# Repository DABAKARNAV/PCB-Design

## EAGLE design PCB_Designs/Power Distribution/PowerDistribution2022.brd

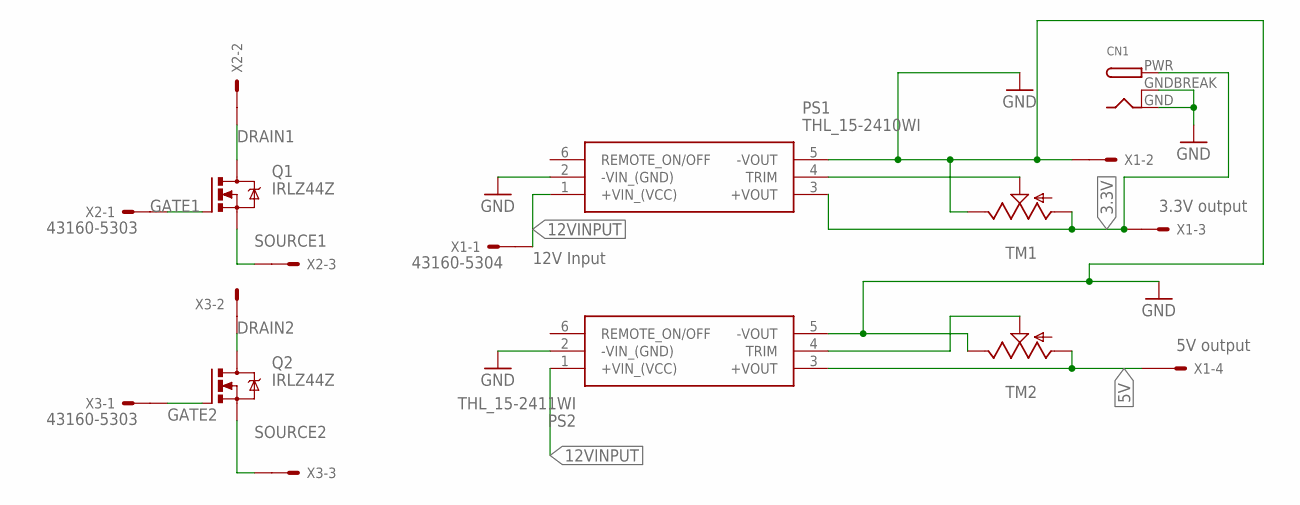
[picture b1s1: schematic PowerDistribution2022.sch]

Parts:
CN1: DCBARRELPTH; DCJACK_2MM_PTH
PS1: THL_15-2410WI; THL152410WI
PS2: THL_15-2411WI; THL152411WI
Q1, Q2: IRLZ44Z; TO220BH
TM1, TM2: TRIM; 6MM
X1: 43160-5304; 43160-XX04
X2, X3: 43160-5303; 43160-XX03

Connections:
3.3V: CN1.PWR, PS1.3 (+VOUT), TM1.A, X1.3@1
5V: PS2.3 (+VOUT), TM2.A, X1.4@1
12VINPUT: PS1.1 (+VIN_(VCC)), PS2.1 (+VIN_(VCC)), X1.1@1
DRAIN1: Q1.D, X2.2@1
DRAIN2: Q2.D, X3.2@1
GATE1: Q1.G, X2.1@1
GATE2: Q2.G, X3.1@1
GND: CN1.GND, CN1.GNDBREAK, PS1.2 (-VIN_(GND)), PS1.5 (-VOUT), PS2.2 (-VIN_(GND)), PS2.5 (-VOUT), TM1.E, TM2.E, X1.2@1
unnamed: PS1.4 (TRIM), TM1.S
unnamed: PS2.4 (TRIM), TM2.S
SOURCE1: Q1.S, X2.3@1
SOURCE2: Q2.S, X3.3@1

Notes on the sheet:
12V Input
5V output
3.3V output

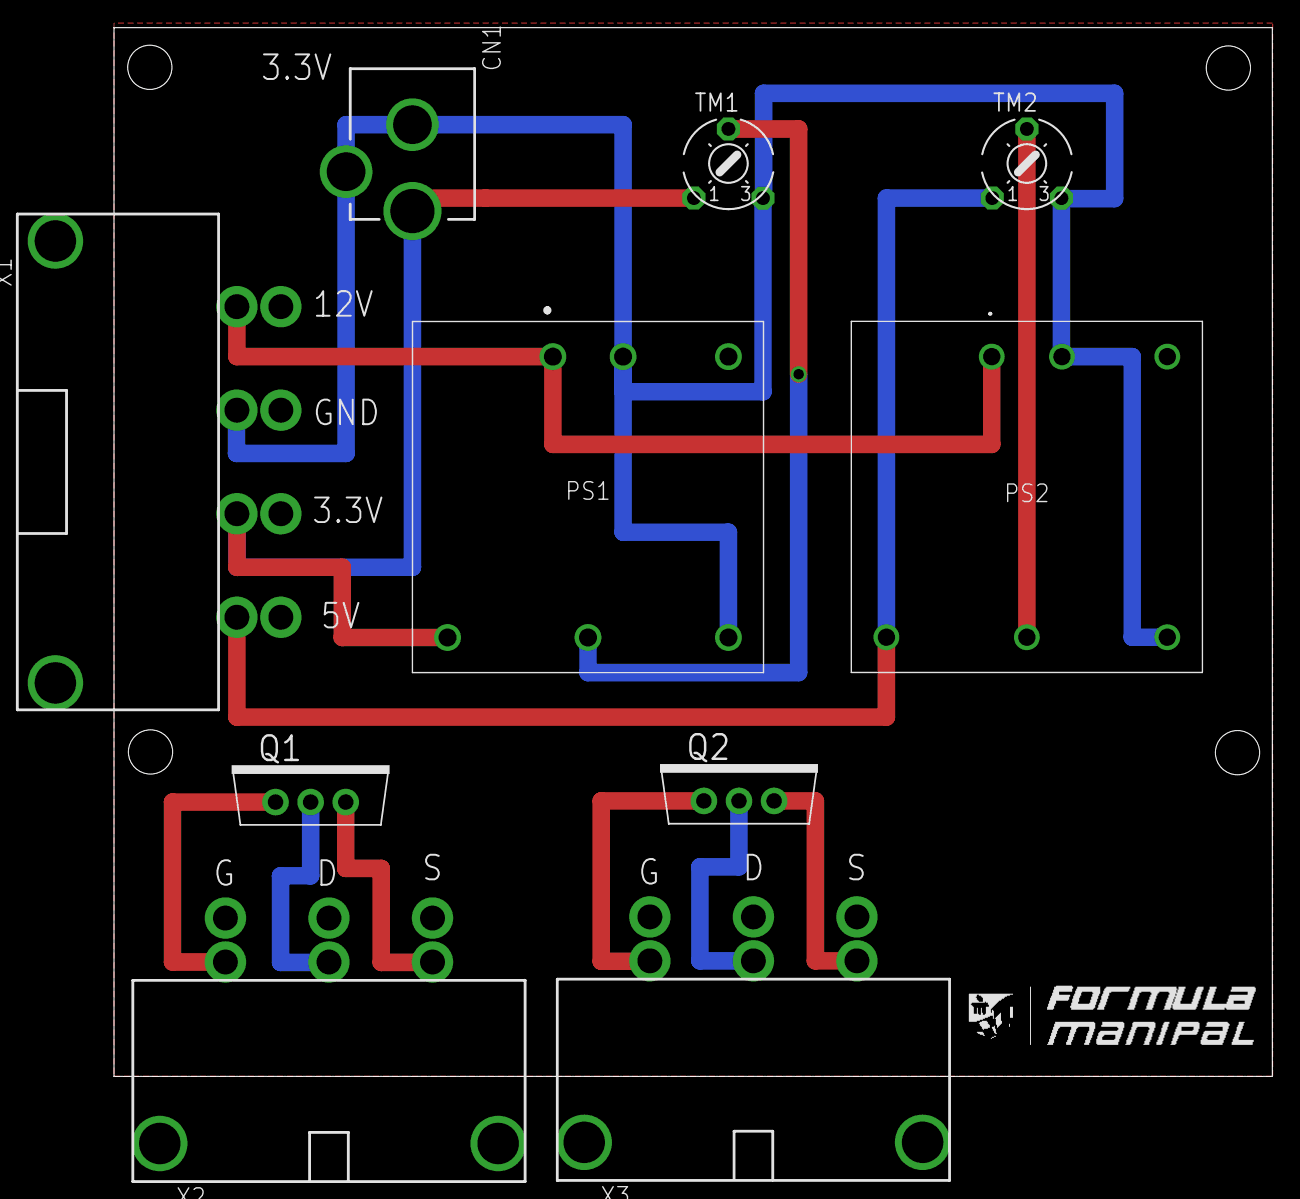
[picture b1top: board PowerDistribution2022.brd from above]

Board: 2 copper layers, 83.8 x 75.9 mm, 10 parts (0 on the bottom side), 12 nets.

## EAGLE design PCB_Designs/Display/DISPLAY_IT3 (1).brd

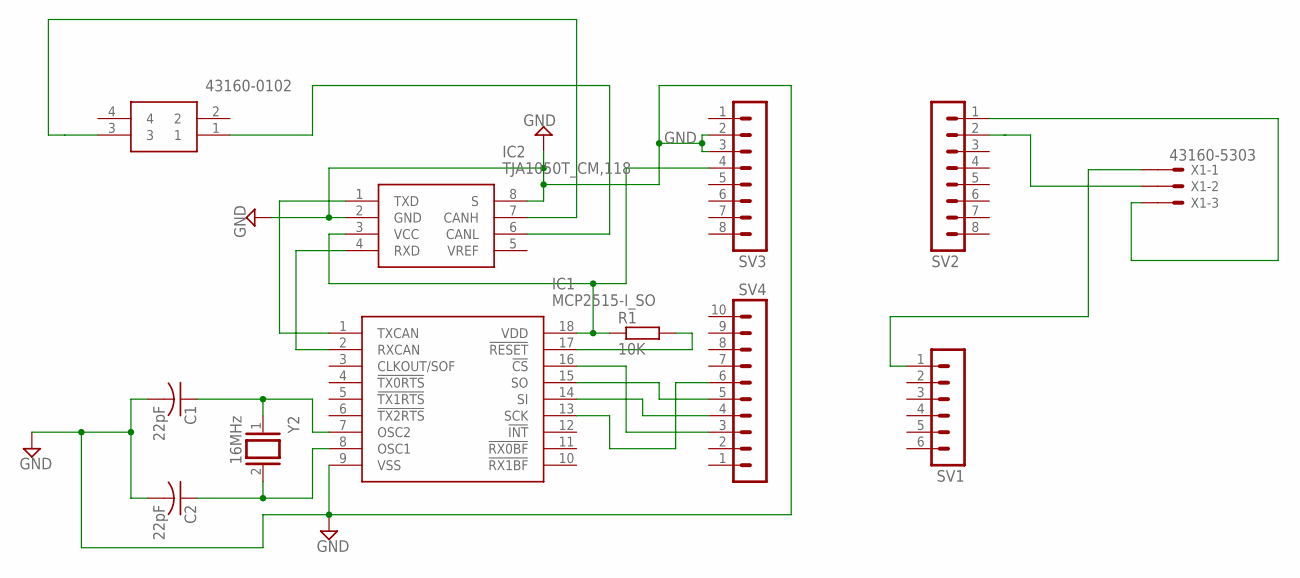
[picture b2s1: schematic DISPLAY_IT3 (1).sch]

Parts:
C1, C2: 22pF; C025-024X044
DIFF_N: 43160-0102; 431600102
IC1: MCP2515-I_SO; SOIC127P1030X265-18N
IC2: TJA1050T_CM,118; SOIC127P600X175-8N
R1: 10K; 0204/7
SV1: MA06-1
SV2, SV3: MA08-1
SV4: MA10-1
X1: 43160-5303; 43160-XX03
Y2: 16MHz; QS

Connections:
DIFF1_N: C2.1, IC1.8 (OSC1), Y2.2
DIFF1_P: C1.1, IC1.7 (OSC2), Y2.1
DIFF_N: DIFF_N.1, IC2.6 (CANL)
DIFF_P: DIFF_N.3, IC2.7 (CANH)
GND: C1.2, C2.2, IC1.9 (VSS), IC2.2 (GND), IC2.8 (S), SV3.2, SV3.3
unnamed: IC1.15 (SO), SV4.5
unnamed: SV2.1, X1.3@1
unnamed: IC1.1 (TXCAN), IC2.1 (TXD)
unnamed: IC1.2 (RXCAN), IC2.4 (RXD)
unnamed: IC1.16 (!CS), SV4.3
unnamed: IC1.14 (SI), SV4.4
unnamed: SV1.1, X1.1@1
unnamed: IC1.13 (SCK), SV4.6
unnamed: IC1.17 (!RESET), R1.2
unnamed: SV2.2, X1.2@1
unnamed: IC1.18 (VDD), IC2.3 (VCC), R1.1, SV3.4

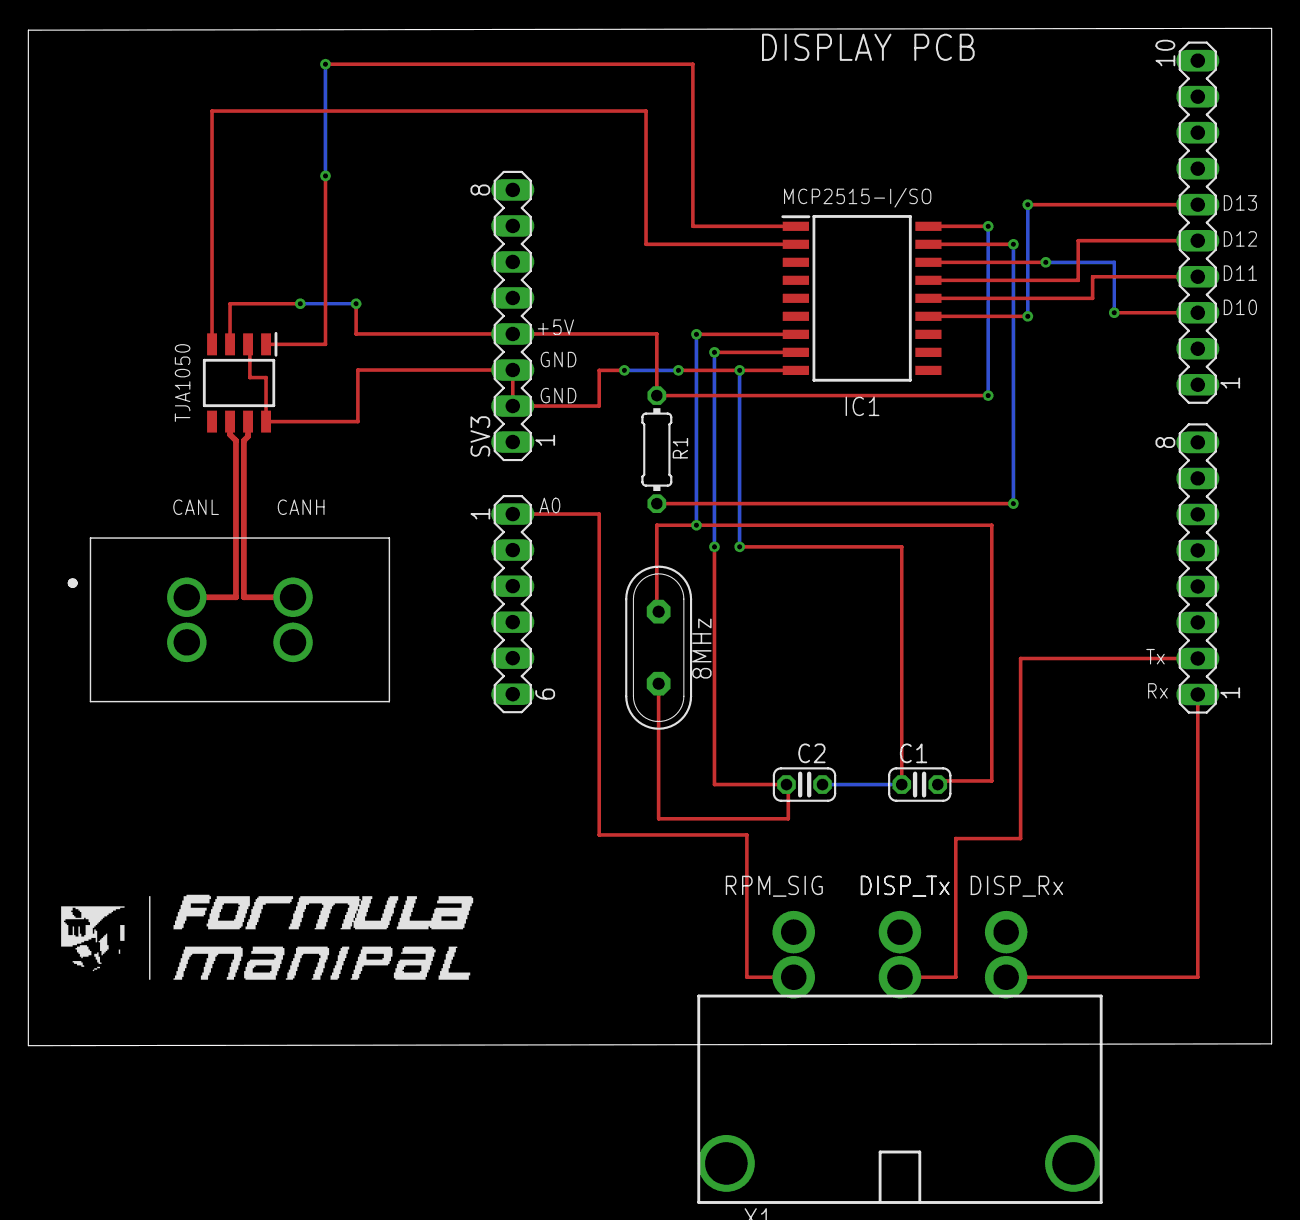
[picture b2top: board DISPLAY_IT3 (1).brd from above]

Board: 2 copper layers, 87.7 x 71.7 mm, 12 parts (0 on the bottom side), 16 nets.

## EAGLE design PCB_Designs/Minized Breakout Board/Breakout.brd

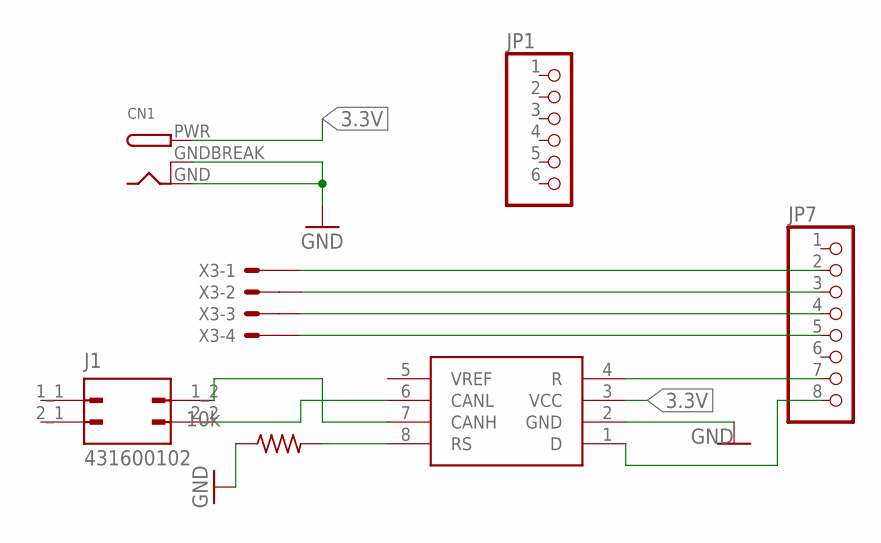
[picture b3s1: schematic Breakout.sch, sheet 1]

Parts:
CN1: DCBARRELPTH; DCJACK_2MM_PTH
IC1: SN65HVD231D; SOIC127P600X175-8N
J1: 431600102; MOLEX_431600102
JP1: PINHD-1X6; 1X06
JP7: PINHD-1X8; 1X08
R5: 10k; 0204/5
X3: 43160-5304; 43160-XX04

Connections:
3.3V: CN1.PWR, IC1.3 (VCC)
GND: CN1.GND, CN1.GNDBREAK, IC1.2 (GND), R5.1
unnamed: IC1.1 (D), JP7.8
unnamed: IC1.4 (R), JP7.7
unnamed: IC1.8 (RS), R5.2
unnamed: JP7.5, X3.4@1
unnamed: JP7.4, X3.3@1
unnamed: JP7.3, X3.2@1
unnamed: JP7.2, X3.1@1
SIG_N: IC1.6 (CANL), J1.2_2
SIG_P: IC1.7 (CANH), J1.1_2

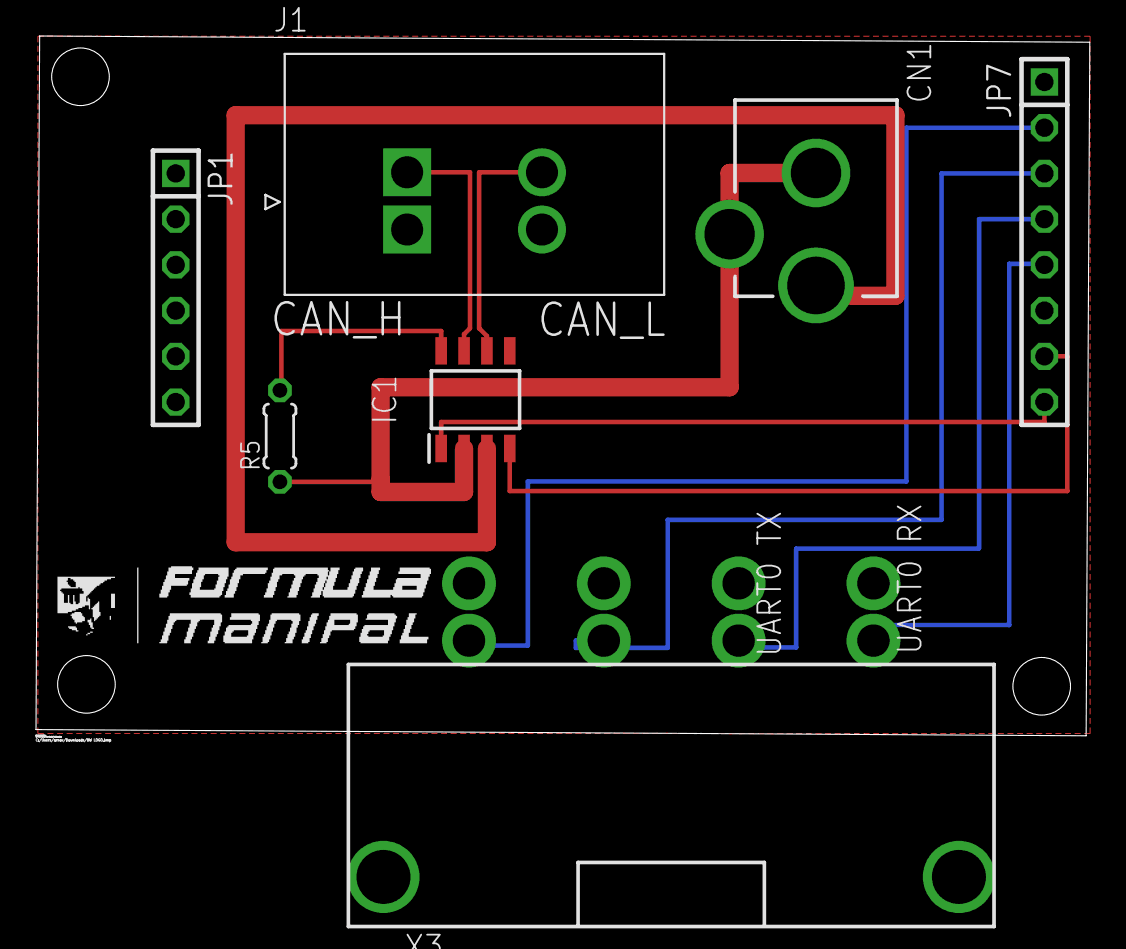
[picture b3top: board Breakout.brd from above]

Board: 2 copper layers, 58.5 x 38.9 mm, 7 parts (0 on the bottom side), 11 nets.

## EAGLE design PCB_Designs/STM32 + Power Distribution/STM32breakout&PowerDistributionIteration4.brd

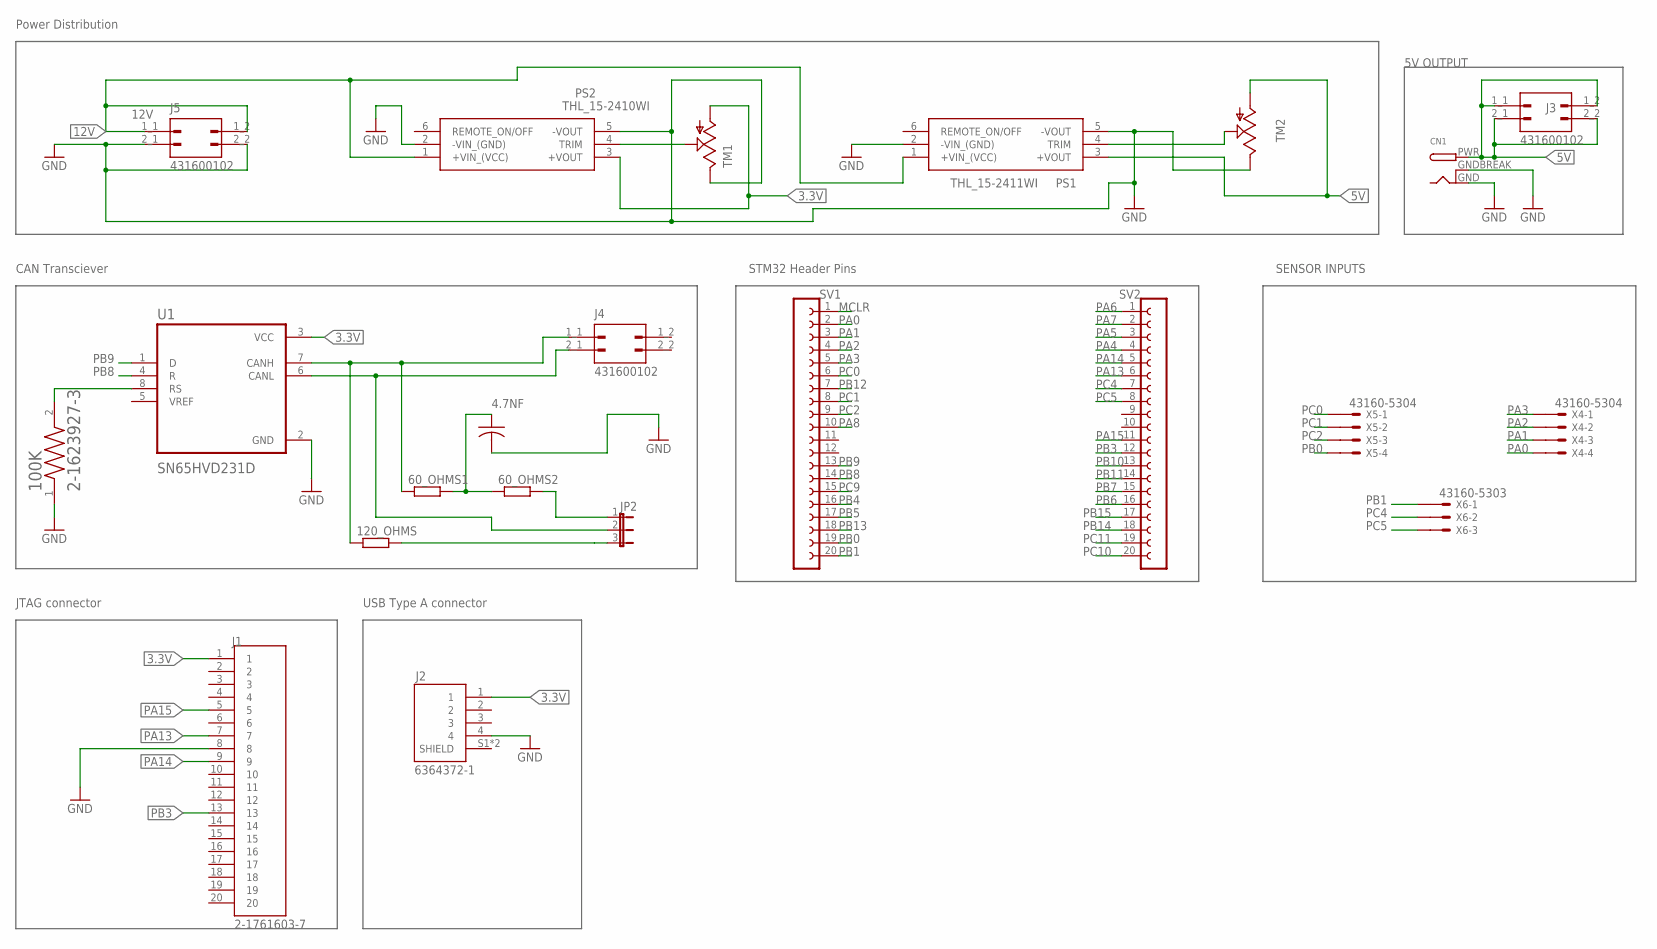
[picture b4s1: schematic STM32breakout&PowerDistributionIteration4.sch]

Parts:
4.7NF: C-US025-030X050; C025-030X050
60_OHMS1, 60_OHMS2, 120_OHMS: R-EU_0204/7; 0204/7
100K: 2-1623927-3; RESAD700W45L350D185
CN1: DCBARRELPTH; DCJACK_2MM_PTH
J1: 2-1761603-7; TE_2-1761603-7
J2: 6364372-1; TE_6364372-1
J3, J4, J5: 431600102; MOLEX_431600102
JP2: JP2W
PS1: THL_15-2411WI; THL152411WI
PS2: THL_15-2410WI; THL152410WI
SV1, SV2: FE20-1; FE20
TM1, TM2: TRIM; 6MM
U1: SN65HVD231D; SOIC127P599X175-8N
X4, X5: 43160-5304; 43160-XX04
X6: 43160-5303; 43160-XX03

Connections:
3.3V: J1.1, J2.1, PS2.3 (+VOUT), TM1.A, U1.3 (VCC)
5V: CN1.PWR, J3.1_1, J3.1_2, J3.2_1, J3.2_2, PS1.3 (+VOUT), TM2.A
12V: J5.1_1, J5.1_2, PS1.1 (+VIN_(VCC)), PS2.1 (+VIN_(VCC))
GND: 4.7NF.2, 100K.1, CN1.GND, CN1.GNDBREAK, J1.8, J2.4, J5.2_1, J5.2_2, PS1.2 (-VIN_(GND)), PS1.5 (-VOUT), PS2.2 (-VIN_(GND)), PS2.5 (-VOUT), TM1.E, TM2.E, U1.2 (GND)
MCLR: SV1.1
unnamed: PS2.4 (TRIM), TM1.S
unnamed: 100K.2, U1.8 (RS)
unnamed: 120_OHMS.2, JP2.3
unnamed: 60_OHMS2.2, JP2.1
unnamed: 4.7NF.1, 60_OHMS1.2, 60_OHMS2.1
unnamed: PS1.4 (TRIM), TM2.S
PA0: SV1.2, X4.4@1
PA1: SV1.3, X4.3@1
PA2: SV1.4, X4.2@1
PA3: SV1.5, X4.1@1
PA4: SV2.4
PA5: SV2.3
PA6: SV2.1
PA7: SV2.2
PA8: SV1.10
PA13: J1.7, SV2.6
PA14: J1.9, SV2.5
PA15: J1.5, SV2.11
PB0: SV1.19, X5.4@1
PB1: SV1.20, X6.1@1
PB3: J1.13, SV2.12
PB4: SV1.16
PB5: SV1.17
PB6: SV2.16
PB7: SV2.15
PB8: SV1.14, U1.4 (R)
PB9: SV1.13, U1.1 (D)
PB10: SV2.13
PB11: SV2.14
PB12: SV1.7
PB13: SV1.18
PB14: SV2.18
PB15: SV2.17
PC0: SV1.6, X5.1@1
PC1: SV1.8, X5.2@1
PC2: SV1.9, X5.3@1
PC4: SV2.7, X6.2@1
PC5: SV2.8, X6.3@1
PC9: SV1.15
PC10: SV2.20
PC11: SV2.19
SIG_N: J4.2_1, JP2.2, U1.6 (CANL)
SIG_P: 60_OHMS1.1, 120_OHMS.1, J4.1_1, U1.7 (CANH)

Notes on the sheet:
Power Distribution
CAN Transciever
STM32 Header Pins
5V OUTPUT
SENSOR INPUTS
JTAG connector
USB Type A connector

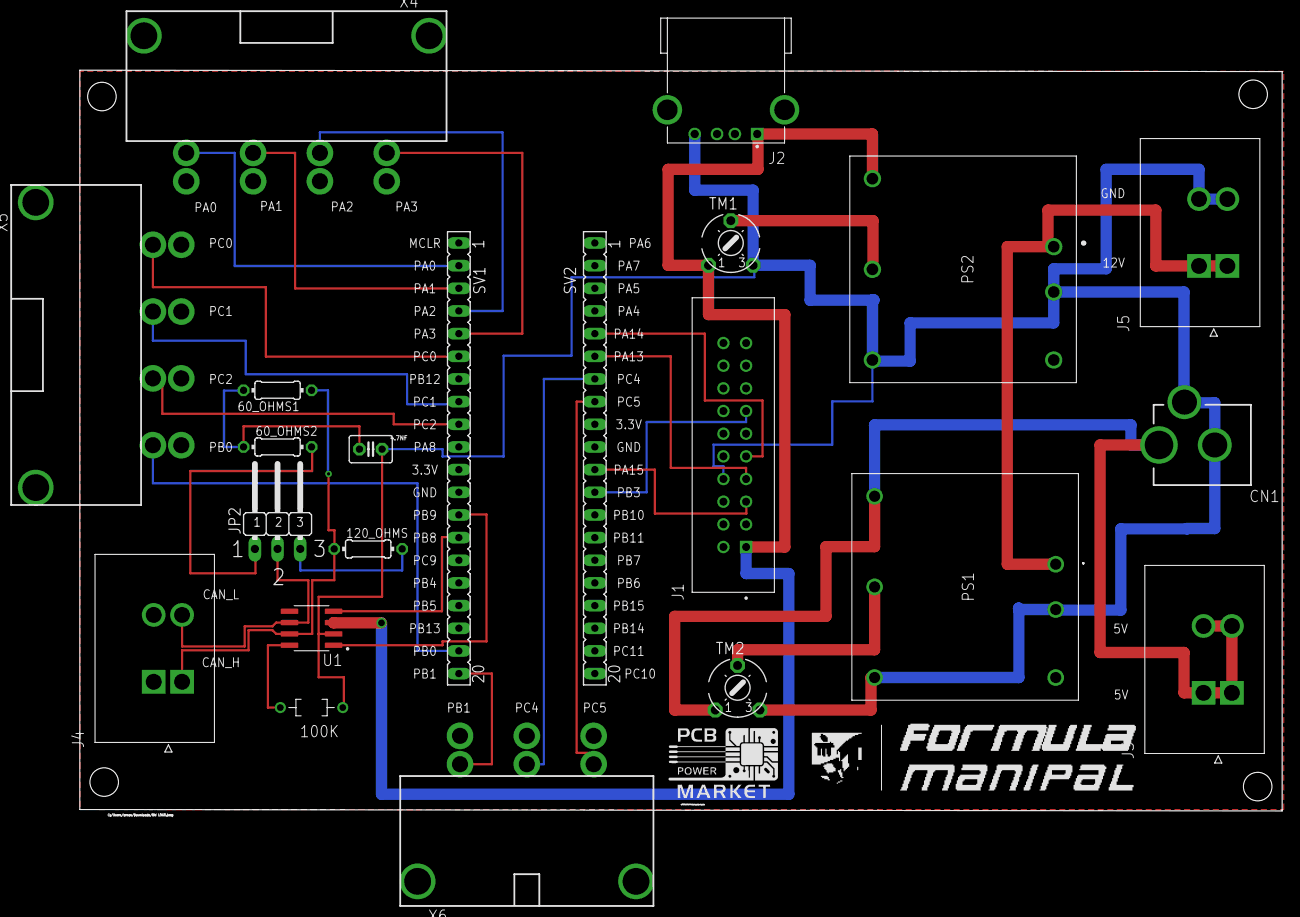
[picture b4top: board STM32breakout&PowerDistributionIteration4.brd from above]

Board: 2 copper layers, 134.8 x 83.0 mm, 22 parts (0 on the bottom side), 29 nets.

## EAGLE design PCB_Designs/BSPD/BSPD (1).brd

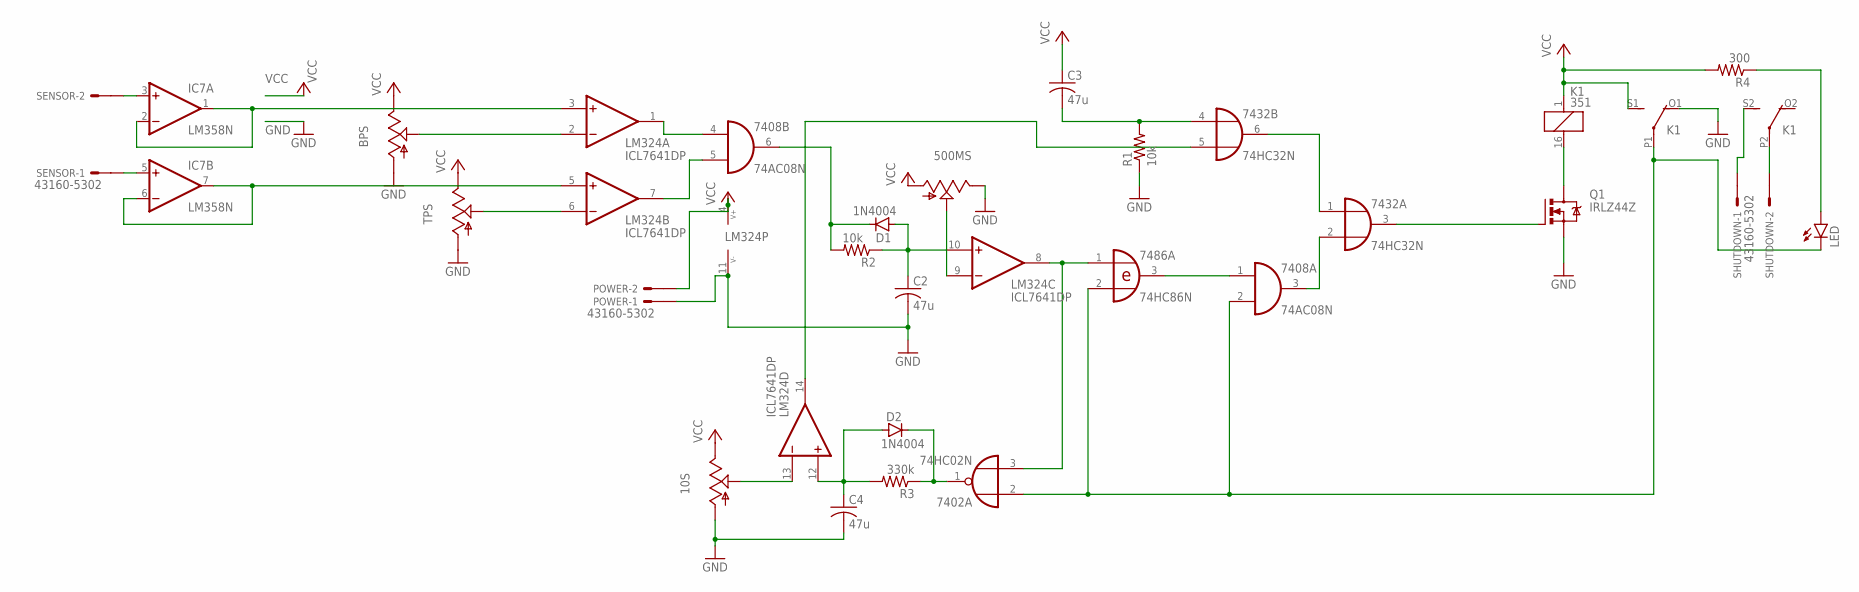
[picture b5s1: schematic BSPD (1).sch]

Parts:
10S, 500MS: TRIM; 6MM
7402: 74HC02N; DIL14
7408: 74AC08N; DIL14
7432: 74HC32N; DIL14
7486: 74HC86N; DIL14
BPS: TRIM; 6MM
C2, C3, C4: 47u; C025-024X044
D1, D2: 1N4004; DO41-10
IC7: LM358N; DIL08
K1: 351
LED: LEDCHIP-LED0805; CHIP-LED0805
LM324: ICL7641DP; DIL14
POWER: 43160-5302; 43160-XX02
Q1: IRLZ44Z; TO220BH
R1, R2: 10k; M0805
R3: 330k; M0805
R4: 300; M0805
SENSOR: 43160-5302; 43160-XX02
SHUTDOWN: 43160-5302; 43160-XX02
TPS: TRIM; 6MM

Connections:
GND: 10S.A, 500MS.E, 7402.7 (GND), 7408.7 (GND), 7432.7 (GND), 7486.7 (GND), BPS.A, C2.2, C4.2, IC7.4 (V-), K1.O1 (O), LM324.11 (V-), POWER.1@1, Q1.S, R1.1, TPS.A
unnamed: BPS.S, LM324.2 (-IN)
unnamed: LM324.6 (-IN), TPS.S
unnamed: LED.A, R4.1
unnamed: 7408.4 (I0), LM324.1 (OUT)
unnamed: 7408.5 (I1), LM324.7 (OUT)
unnamed: 7408.6 (O), D1.C, R2.2
unnamed: C2.1, D1.A, LM324.10 (+IN), R2.1
unnamed: 500MS.S, LM324.9 (-IN)
unnamed: 7402.3 (I1), 7486.1 (I0), LM324.8 (OUT)
unnamed: 7408.1 (I0), 7486.3 (O)
unnamed: 7408.3 (O), 7432.2 (I1)
unnamed: 7432.4 (I0), C3.2, R1.2
unnamed: 7432.1 (I0), 7432.6 (O)
unnamed: 7432.3 (O), Q1.G
unnamed: K1.16 (2), Q1.D
unnamed: 10S.S, LM324.13 (-IN)
unnamed: C4.1, D2.A, LM324.12 (+IN), R3.2
unnamed: 7402.1 (O), D2.C, R3.1
unnamed: K1.P2, SHUTDOWN.2@1
unnamed: K1.S2 (S), SHUTDOWN.1@1
unnamed: 7432.5 (I1), LM324.14 (OUT)
unnamed: 7402.2 (I0), 7408.2 (I1), 7486.2 (I1), K1.P1, LED.C
unnamed: IC7.3 (+IN), SENSOR.2@1
unnamed: IC7.5 (+IN), SENSOR.1@1
unnamed: IC7.1 (OUT), IC7.2 (-IN), LM324.3 (+IN)
unnamed: IC7.6 (-IN), IC7.7 (OUT), LM324.5 (+IN)
VCC: 10S.E, 500MS.A, 7402.14 (VCC), 7408.14 (VCC), 7432.14 (VCC), 7486.14 (VCC), BPS.E, C3.1, IC7.8 (V+), K1.1, K1.S1 (S), LM324.4 (V+), POWER.2@1, R4.2, TPS.E

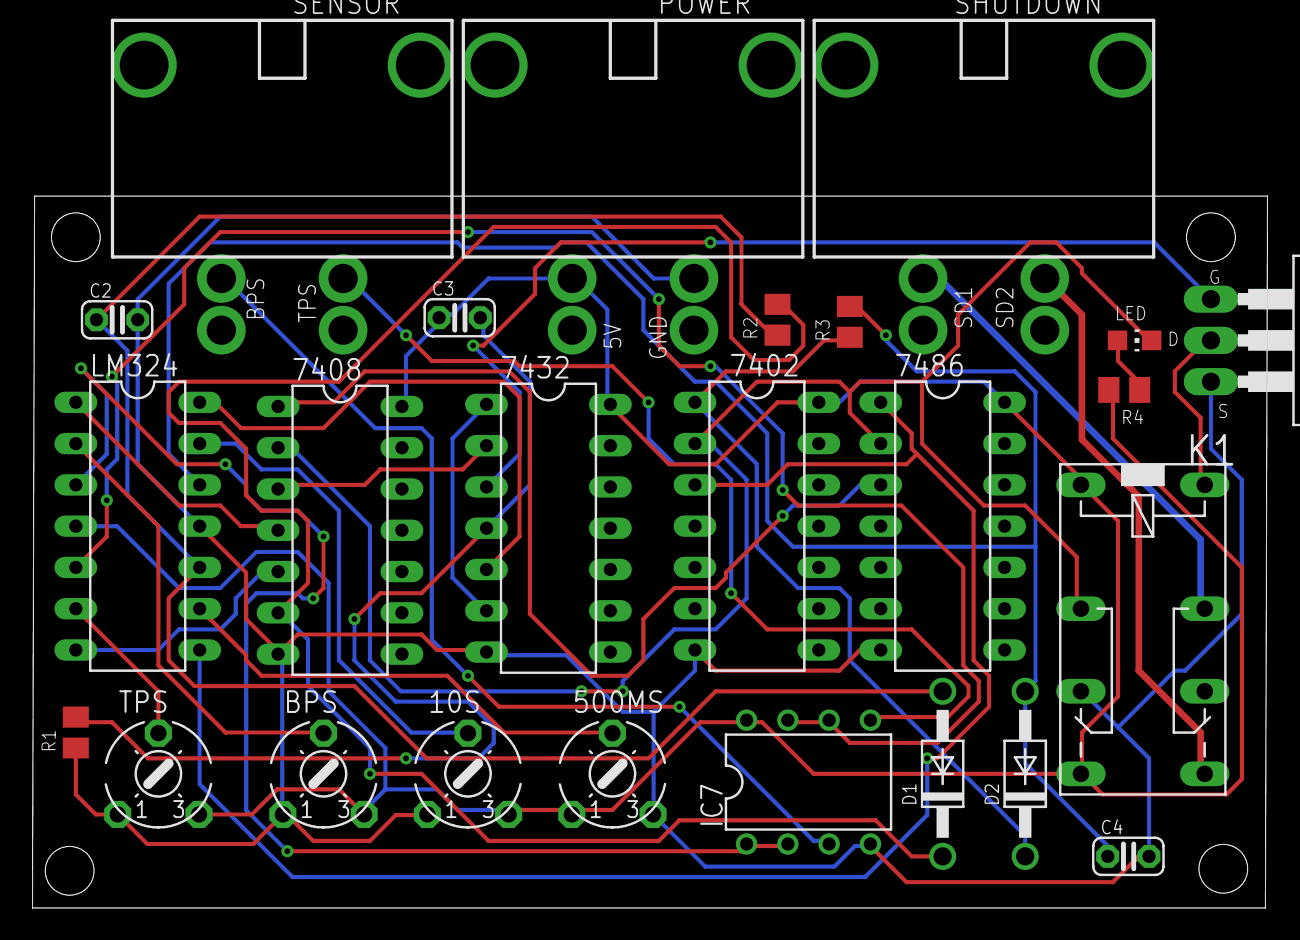
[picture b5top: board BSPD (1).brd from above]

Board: 2 copper layers, 76.0 x 43.8 mm, 25 parts (0 on the bottom side), 28 nets.

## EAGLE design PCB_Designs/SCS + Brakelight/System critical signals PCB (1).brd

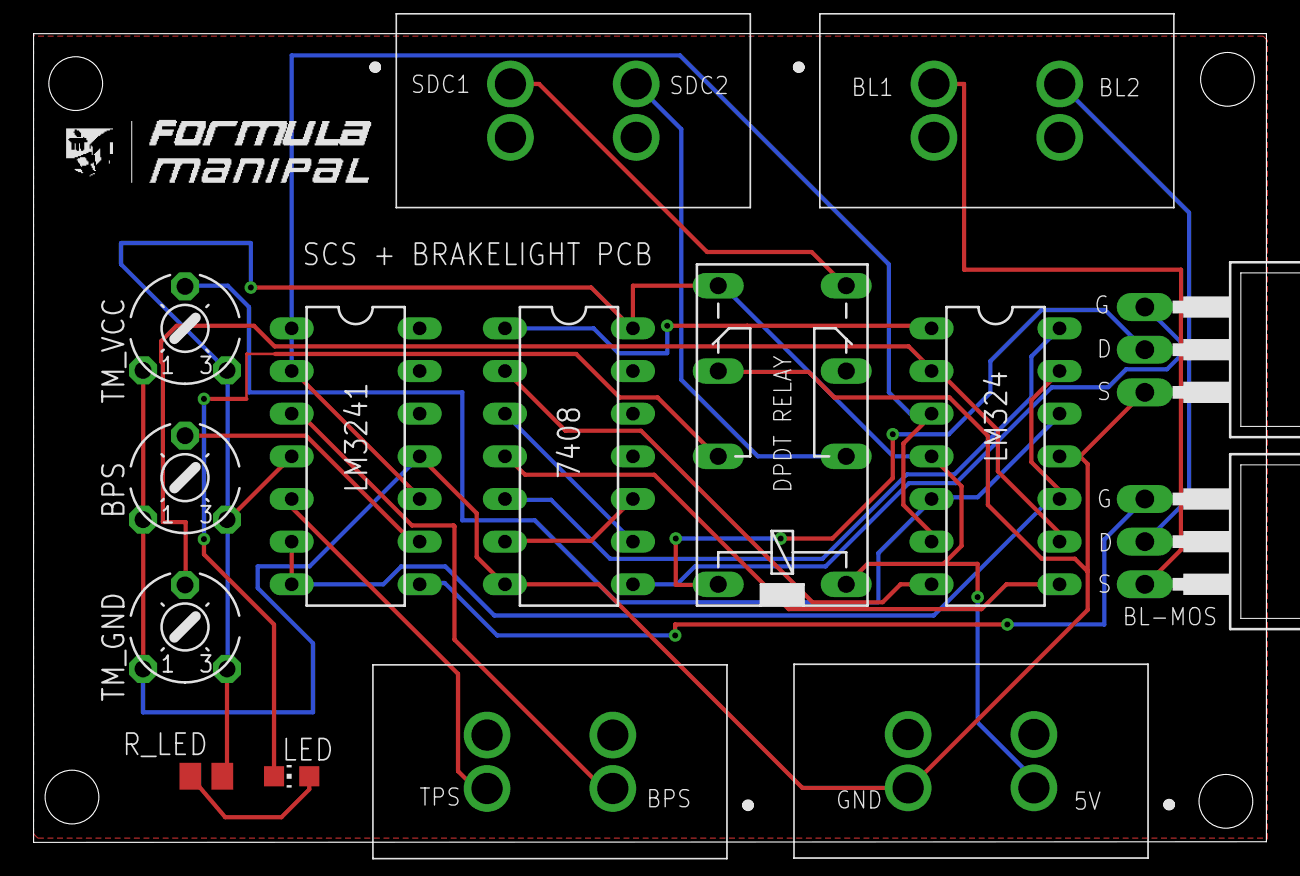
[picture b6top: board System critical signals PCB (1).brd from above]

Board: 2 copper layers, 73.4 x 48.2 mm, 15 parts (0 on the bottom side), 24 nets.

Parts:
7408: 74HC08N; DIL14
BPS: 6MM
J1, J2, J3, J4: 43160-0102; 431600102
K1: 351
LED: CHIP-LED0805
LM324, LM3241: ICL7641DP; DIL14
Q1, Q2: IRLZ44Z; TO220BH
R_LED: 300; M0805
TM_GND: 6MM
TM_VCC: 6MM

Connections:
GND: 7408.7, BPS.A, J1.3, K1.O2, LM324.11, LM3241.11, Q1.S, TM_GND.A, TM_VCC.A
unnamed: 7408.4, LM324.8
unnamed: LM324.3, LM324.6, LM3241.1, LM3241.2, LM3241.10
unnamed: LM324.10, LM324.13, LM3241.6, LM3241.7
unnamed: 7408.5, LM324.14
unnamed: 7408.1, LM324.1
unnamed: 7408.2, LM324.7
unnamed: 7408.3, 7408.9
unnamed: 7408.6, 7408.10
unnamed: 7408.8, Q1.G
unnamed: K1.16, Q1.D
unnamed: J4.1, K1.S1
unnamed: J4.3, K1.P1
unnamed: LED.A, R_LED.1
unnamed: BPS.S, LM3241.9
unnamed: LM3241.8, Q2.G
unnamed: J3.3, Q2.D
unnamed: J3.1, Q2.S
unnamed: K1.P2, LED.C
unnamed: J2.1, LM3241.3
unnamed: J2.3, LM3241.5
unnamed: LM324.2, LM324.9, TM_GND.S
unnamed: LM324.5, LM324.12, TM_VCC.S
VCC: 7408.14, BPS.E, J1.1, K1.1, K1.S2, LM324.4, LM3241.4, R_LED.2, TM_GND.E, TM_VCC.E

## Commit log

2022-09-11 Create BSPD
2022-09-11 PCB-Design/SCS
